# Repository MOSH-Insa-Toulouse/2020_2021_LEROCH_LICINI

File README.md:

# 2020_2021_LEROCH_LICINI

### KiCad

[KiCad EDA - Schematic Capture & PCB Design Software](https://kicad-pcb.org/), version: 5.1.7

Open source EDA / electronics CAD software for Windows, macOS and Linux.

## Electrical diagram

## Components placement

## 3D view

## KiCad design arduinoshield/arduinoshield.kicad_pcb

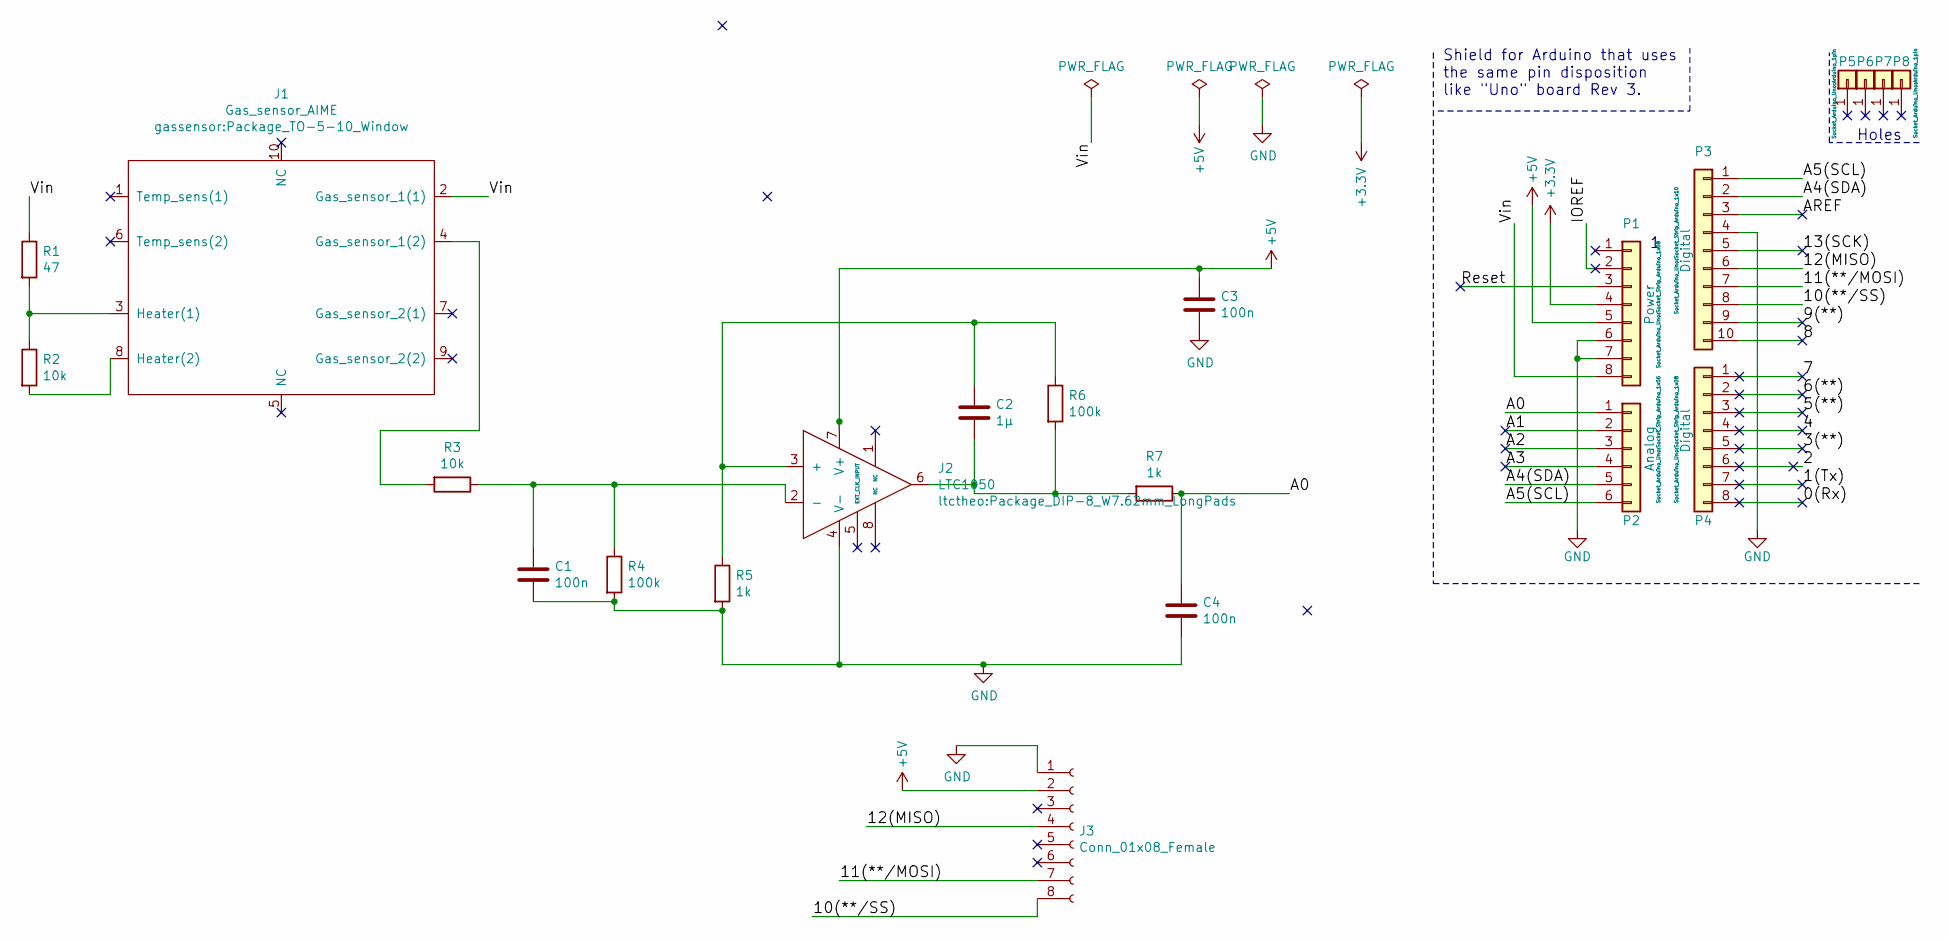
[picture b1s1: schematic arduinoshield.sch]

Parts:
C1, C3, C4: 100n; CP_Axial_L10.0mm_D4.5mm_P15.00mm_Horizontal
C2: 1µ; CP_Axial_L10.0mm_D4.5mm_P15.00mm_Horizontal
J1: Gas_sensor_AIME; Package_TO-5-10_Window
J2: LTC1050; Package_DIP-8_W7.62mm_LongPads
J3: Conn_01x08_Female; PinHeader_1x08_P2.54mm_Vertical
P1: Power; Socket_Strip_Arduino_1x08
P2: Analog; Socket_Strip_Arduino_1x06
P3: Digital; Socket_Strip_Arduino_1x10
P4: Digital; Socket_Strip_Arduino_1x08
P5, P6, P7, P8: CONN_01X01; Arduino_1pin
R1: 47; R_Axial_DIN0207_L6.3mm_D2.5mm_P10.16mm_Horizontal
R2, R3: 10k; R_Axial_DIN0207_L6.3mm_D2.5mm_P10.16mm_Horizontal
R4, R6: 100k; R_Axial_DIN0207_L6.3mm_D2.5mm_P10.16mm_Horizontal
R5, R7: 1k; R_Axial_DIN0207_L6.3mm_D2.5mm_P10.16mm_Horizontal

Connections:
+3V3: P1.4
+5V: C3.1, J2.7 (V+), J3.2, P1.5
/0(Rx): P4.8
/1(Tx): P4.7
/2: P4.6
/3(**): P4.5
/4: P4.4
/5(**): P4.3
/6(**): P4.2
/7: P4.1
/8: P3.10
/9(**): P3.9
/10(**/SS): J3.8, P3.8
/11(**/MOSI): J3.7, P3.7
/12(MISO): J3.4, P3.6
/13(SCK): P3.5
/A0: C4.1, P2.1, R7.1
/A1: P2.2
/A2: P2.3
/A3: P2.4
/A4(SDA): P2.5, P3.2
/A5(SCL): P2.6, P3.1
/AREF: P3.3
/IOREF: P1.2
/Reset: P1.3
/Vin: J1.2 (Gas_sensor_1(1)), P1.8, R1.1
GND: C1.2, C3.2, C4.2, J2.4 (V-), J3.1, P1.6, P1.7, P3.4, R4.2, R5.2
unnamed: C1.1, J2.2 (-), R3.1, R4.1
unnamed: C2.1, J2.3 (+), R5.1, R6.1
unnamed: C2.2, J2.6, R6.2, R7.2
unnamed: J1.3 (Heater(1)), R1.2, R2.1
unnamed: J1.4 (Gas_sensor_1(2)), R3.2
unnamed: J1.8 (Heater(2)), R2.2

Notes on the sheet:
Holes
Shield for Arduino that uses the same pin disposition like "Uno" board Rev 3.

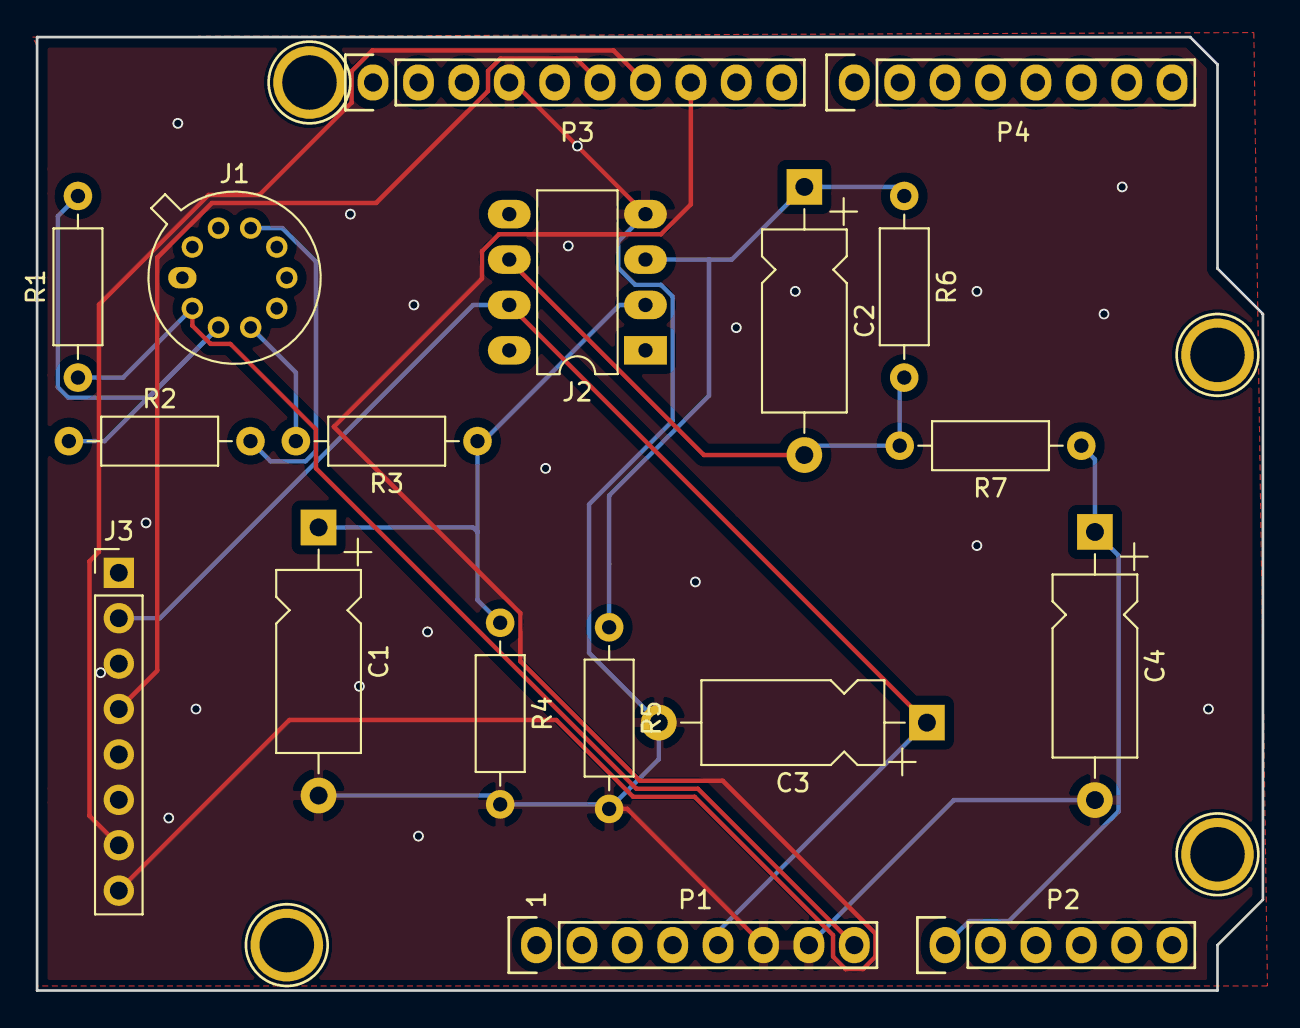
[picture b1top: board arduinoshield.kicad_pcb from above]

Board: 2 copper layers, 68.6 x 53.3 mm, 22 parts (0 on the bottom side), 15 nets.

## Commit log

2021-01-09 Add kicad project
2021-01-09 add pcb images
2021-01-09 new photos
2021-01-09 add lora headers
